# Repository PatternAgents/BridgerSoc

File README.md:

BridgerSoc
==========
PatternAgents BridgerSoc Control Shield for Arduino

[  
*PatternAgents BridgerSoc*](http://www.patternagents.com/projects/BridgerSoc.html)

PatternAgents The BridgerSoc uses a Programmable System-on-Chip that can read read inputs from sensors, 
switches, potentiometers, or other analog inputs and use those inputs to control the outputs of your choice.

Features:

  System-on-Chip Standalone Mode (Switches/Analog Inputs Control the Outputs)

  Arduino Uno/Leonardo/Mega/Due Compatible Shield

  Selectable 3.3Volt-5.0Volt Operation

  Sixteen (16) high power darlington control outputs

  Seven (7) analog inputs (sensors, potentiometers)

  Five (5) digital inputs (switches, sensors)

  UART, I2C, SPI, RS-485/DMX Interfaces

  Selectable mode of operation  (Manual or Interface/Shield controlled)

You can read more about the PSoC1 Integrated Circuit used here : http://www.cypress.com/?mpn=CY8C29566-24AXI

[  
*Licensing CC BY-NC-SA 4.0*](http://creativecommons.org/licenses/by-nc-sa/4.0/)

PatternAgents uses the increasingly popular business model called "Dual Licensing" 
in which both the open source software distribution mechanism and traditional commercial software distribution models are combined.

Open Source Projects:        

If you are developing and distributing open source applications under the Creative Commons CC BY-NC-SA 4.0, 
as published by the Creative Commons Foundation, then you are free to use the PatternAgents hardware/software under the CC BY-NC-SA 4.0 license. 
Please note that CC BY-NC-SA 4.0 requires that all modifications to the original code as well as all Derivative Works 
must also be released under the terms of the CC BY-NC-SA 4.0 license.

Closed Source Projects:

If you are developing and distributing traditional closed source or commercial applications, 
you must purchase a PatternAgents commercial use license, 
which is specifically designed for users interested in retaining the proprietary status of their designs and code. 
All PatternAgents commercial licenses expressly supersede the CC BY-NC-SA 4.0 license. 
This means that when you license the PatternAgents software under a commercial license, 
you specifically do not use the software under the CC BY-NC-SA 4.0 license and therefore you are not subject to any of its terms.
        
If you would like to use our designs for your own personal or educational use, have at it! 

Our public design repository is available at <a href="https://github.com/patternagents">Github</a>.

If you would like to produce our designs for commercial use, or as products for sale, 
please contact us to arrange for a Commercial Use license. We have many other designs, 
as well as options and extras that are not released publicly. 
We will also customize designs, firmware, and software for a reasonable fee, just contact us to discuss your requirements.

THIS SOFTWARE IS PROVIDED BY THE CONTRIBUTORS "AS IS" AND WITHOUT ANY EXPRESS OR IMPLIED WARRANTIES, 
INCLUDING, BUT NOT LIMITED TO, THE IMPLIED WARRANTIES OF MERCHANTABILITY AND FITNESS FOR A PARTICULAR PURPOSE ARE DISCLAIMED. 
IN NO EVENT SHALL THE COPYRIGHT OWNER OR CONTRIBUTORS BE LIABLE FOR ANY DIRECT, INDIRECT, INCIDENTAL, SPECIAL, EXEMPLARY, 
OR CONSEQUENTIAL DAMAGES (INCLUDING, BUT NOT LIMITED TO, PROCUREMENT OF SUBSTITUTE GOODS OR SERVICES; LOSS OF USE, DATA, 
OR PROFITS; OR BUSINESS INTERRUPTION) HOWEVER CAUSED AND ON ANY THEORY OF LIABILITY, WHETHER IN CONTRACT, 
STRICT LIABILITY, OR TORT (INCLUDING NEGLIGENCE OR OTHERWISE) ARISING IN ANY WAY OUT OF THE USE OF THIS SOFTWARE, 
EVEN IF ADVISED OF THE POSSIBILITY OF SUCH DAMAGE. 

-------------------------------------------------------------------------------------------

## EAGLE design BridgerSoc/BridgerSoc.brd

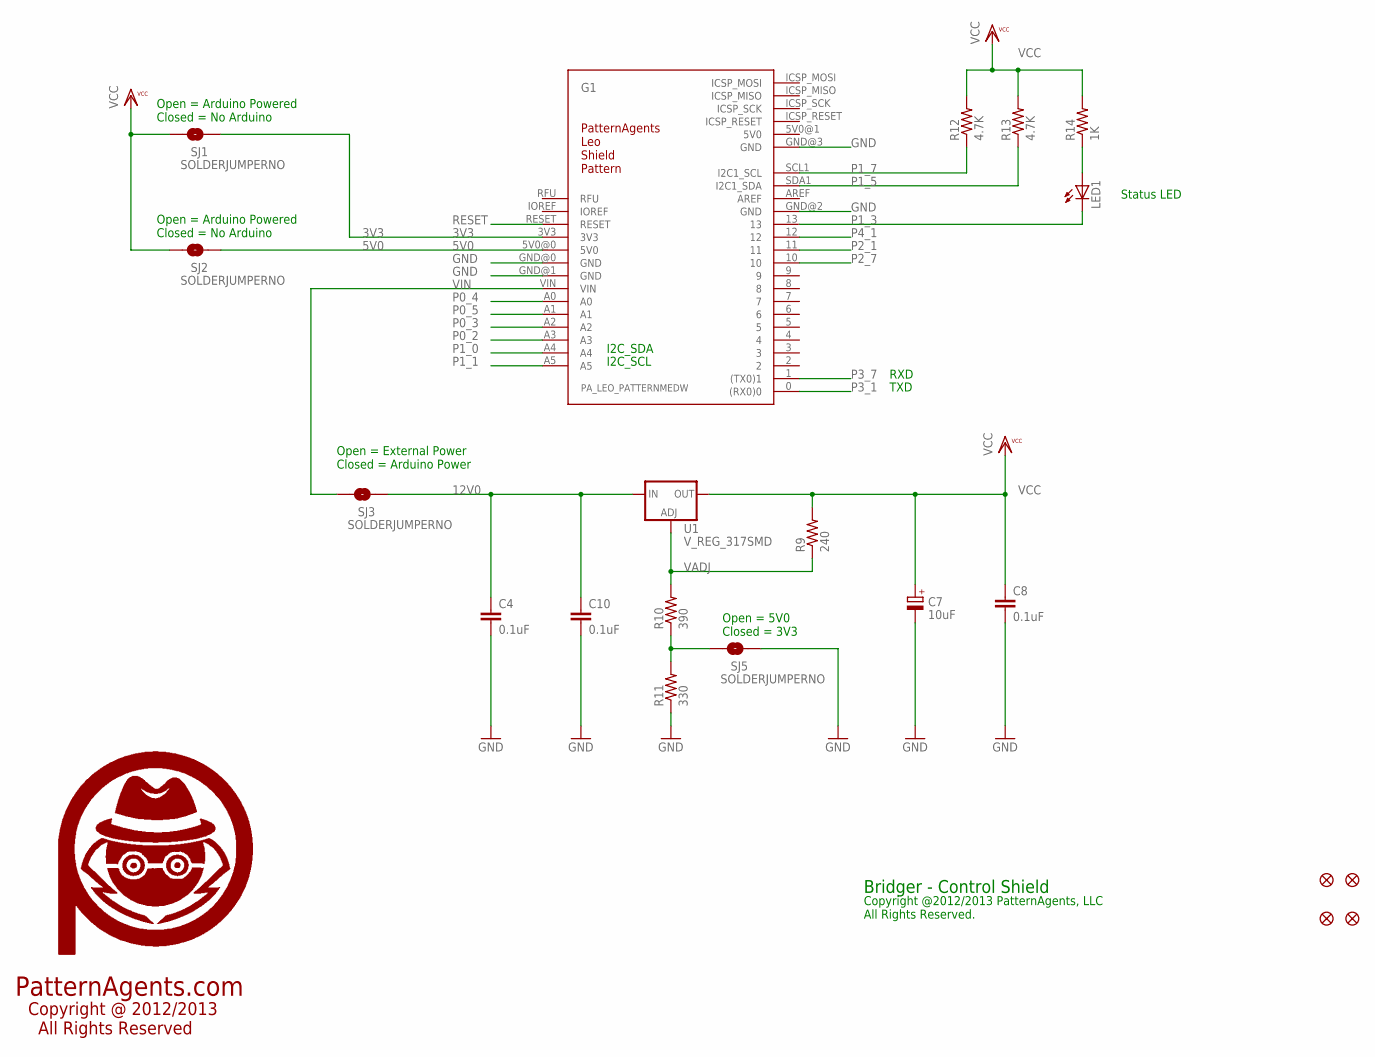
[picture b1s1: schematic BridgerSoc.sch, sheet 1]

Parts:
C4, C8, C10: 0.1uF; 0603-CAP
C7: 10uF; SMC_B
FID1, FID2, FID3, FID4: FIDUCIAL1.5X3; FIDUCIAL-1.5X3
G1: PA_LEO_PATTERNMEDW; PA_LEO_MEDW_PATTERN
LED1: LED0603; LED-0603
R9: 240; R0603
R10: 390; R0603
R11: 330; R0603
R12, R13: 4.7K; R0603
R14: 1K; R0603
SJ1, SJ2, SJ3, SJ5: SOLDERJUMPERNO; SJ_2S-NO
U1: V_REG_317SMD; SOT223
U$1: PA_LOGO_SYMLARGE; PA_LOGO_AGENT_LRG_SYM

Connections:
3V3: G1.3V3, SJ1.1
5V0: G1.5V0@0 (5V0), G1.5V0@1 (5V0), SJ2.1
12V0: C4.1, C10.1, SJ3.1, U1.3 (IN); also elsewhere on the board
GND: C4.2, C7.-, C8.2, C10.2, G1.GND@0 (GND), G1.GND@1 (GND), G1.GND@2 (GND), G1.GND@3 (GND), R11.1, SJ5.1; also elsewhere on the board
LED_D13: LED1.A, R14.1
P0_2: G1.A3; also elsewhere on the board
P0_3: G1.A2; also elsewhere on the board
P0_4: G1.A0; also elsewhere on the board
P0_5: G1.A1; also elsewhere on the board
P1_0: G1.A4; also elsewhere on the board
P1_1: G1.A5; also elsewhere on the board
P1_3: G1.13, LED1.C; also elsewhere on the board
P1_5: G1.SDA1 (I2C1_SDA), R13.1; also elsewhere on the board
P1_7: G1.SCL1 (I2C1_SCL), R12.1; also elsewhere on the board
P2_1: G1.11; also elsewhere on the board
P2_7: G1.10; also elsewhere on the board
P3_1: G1.0 ((RX0)0); also elsewhere on the board
P3_7: G1.1 ((TX0)1); also elsewhere on the board
P4_1: G1.12; also elsewhere on the board
RESET: G1.RESET
RFU: G1.RFU
V3_5: R10.1, R11.2, SJ5.2
VADJ: R9.1, R10.2, U1.1 (ADJ)
VCC: C7.+, C8.1, R9.2, R12.2, R13.2, R14.2, SJ1.2, SJ2.2, U1.2 (OUT); also elsewhere on the board
VIN: G1.VIN, SJ3.2

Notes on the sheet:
PatternAgents.com
Copyright @ 2012/2013 All Rights Reserved
Bridger - Control Shield
Copyright @2012/2013 PatternAgents, LLC All Rights Reserved.
I2C_SDA
I2C_SCL
Open = 5V0 Closed = 3V3
Open = External Power Closed = Arduino Power
Open = Arduino Powered Closed = No Arduino
TXD
RXD
Status LED

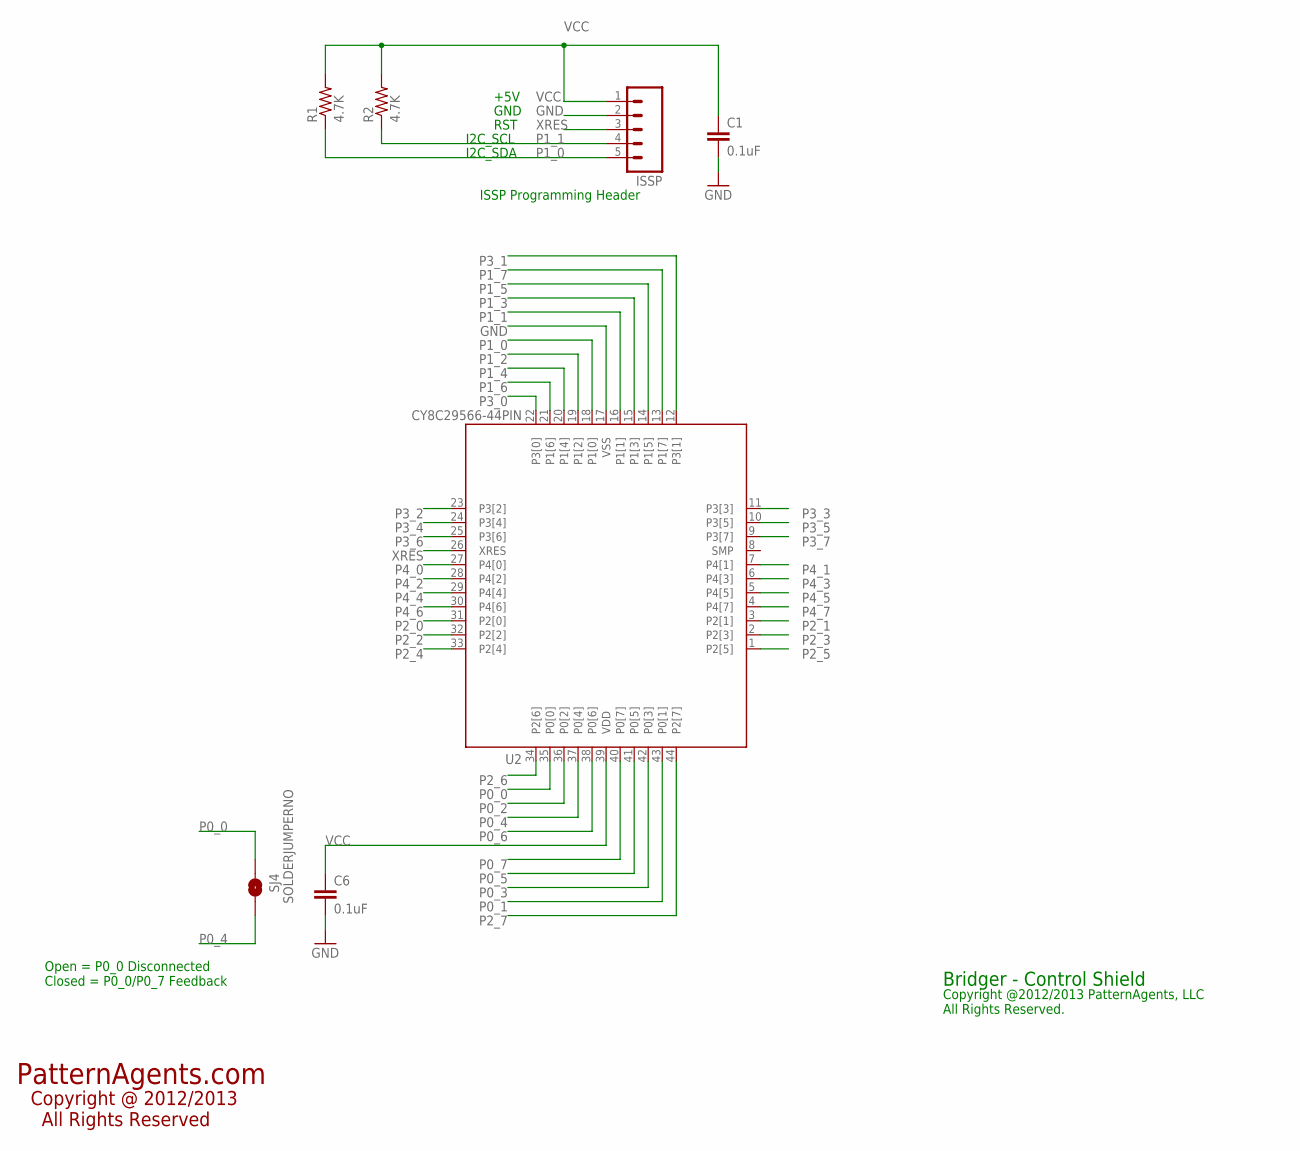
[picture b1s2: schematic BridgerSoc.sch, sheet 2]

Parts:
C1, C6: 0.1uF; 0603-CAP
ISSP: M05PTH; 1X05
R1, R2: 4.7K; R0603
SJ4: SOLDERJUMPERNO; SJ_2S-NO
U2: CY8C29566-44PIN; TQFP-10X10-44

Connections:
GND: C1.2, C6.2, ISSP.2, U2.17 (VSS); also elsewhere on the board
P0_0: SJ4.1, U2.35 (P0[0])
P0_1: U2.43 (P0[1]); also elsewhere on the board
P0_2: U2.36 (P0[2]); also elsewhere on the board
P0_3: U2.42 (P0[3]); also elsewhere on the board
P0_4: SJ4.2, U2.37 (P0[4]); also elsewhere on the board
P0_5: U2.41 (P0[5]); also elsewhere on the board
P0_6: U2.38 (P0[6]); also elsewhere on the board
P0_7: U2.40 (P0[7]); also elsewhere on the board
P1_0: ISSP.5, R1.1, U2.18 (P1[0]); also elsewhere on the board
P1_1: ISSP.4, R2.1, U2.16 (P1[1]); also elsewhere on the board
P1_2: U2.19 (P1[2]); also elsewhere on the board
P1_3: U2.15 (P1[3]); also elsewhere on the board
P1_4: U2.20 (P1[4]); also elsewhere on the board
P1_5: U2.14 (P1[5]); also elsewhere on the board
P1_6: U2.21 (P1[6]); also elsewhere on the board
P1_7: U2.13 (P1[7]); also elsewhere on the board
P2_0: U2.31 (P2[0]); also elsewhere on the board
P2_1: U2.3 (P2[1]); also elsewhere on the board
P2_2: U2.32 (P2[2]); also elsewhere on the board
P2_3: U2.2 (P2[3]); also elsewhere on the board
P2_4: U2.33 (P2[4]); also elsewhere on the board
P2_5: U2.1 (P2[5]); also elsewhere on the board
P2_6: U2.34 (P2[6]); also elsewhere on the board
P2_7: U2.44 (P2[7]); also elsewhere on the board
P3_0: U2.22 (P3[0]); also elsewhere on the board
P3_1: U2.12 (P3[1]); also elsewhere on the board
P3_2: U2.23 (P3[2]); also elsewhere on the board
P3_3: U2.11 (P3[3]); also elsewhere on the board
P3_4: U2.24 (P3[4]); also elsewhere on the board
P3_5: U2.10 (P3[5]); also elsewhere on the board
P3_6: U2.25 (P3[6]); also elsewhere on the board
P3_7: U2.9 (P3[7]); also elsewhere on the board
P4_0: U2.27 (P4[0]); also elsewhere on the board
P4_1: U2.7 (P4[1]); also elsewhere on the board
P4_2: U2.28 (P4[2]); also elsewhere on the board
P4_3: U2.6 (P4[3]); also elsewhere on the board
P4_4: U2.29 (P4[4]); also elsewhere on the board
P4_5: U2.5 (P4[5]); also elsewhere on the board
P4_6: U2.30 (P4[6]); also elsewhere on the board
P4_7: U2.4 (P4[7]); also elsewhere on the board
SMP: U2.8 (SMP)
VCC: C1.1, C6.1, ISSP.1, R1.2, R2.2, U2.39 (VDD); also elsewhere on the board
XRES: ISSP.3, U2.26 (XRES)

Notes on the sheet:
PatternAgents.com
Copyright @ 2012/2013 All Rights Reserved
Bridger - Control Shield
Copyright @2012/2013 PatternAgents, LLC All Rights Reserved.
ISSP Programming Header
I2C_SDA
I2C_SCL
RST
GND
+5V
Open = P0_0 Disconnected Closed = P0_0/P0_7 Feedback

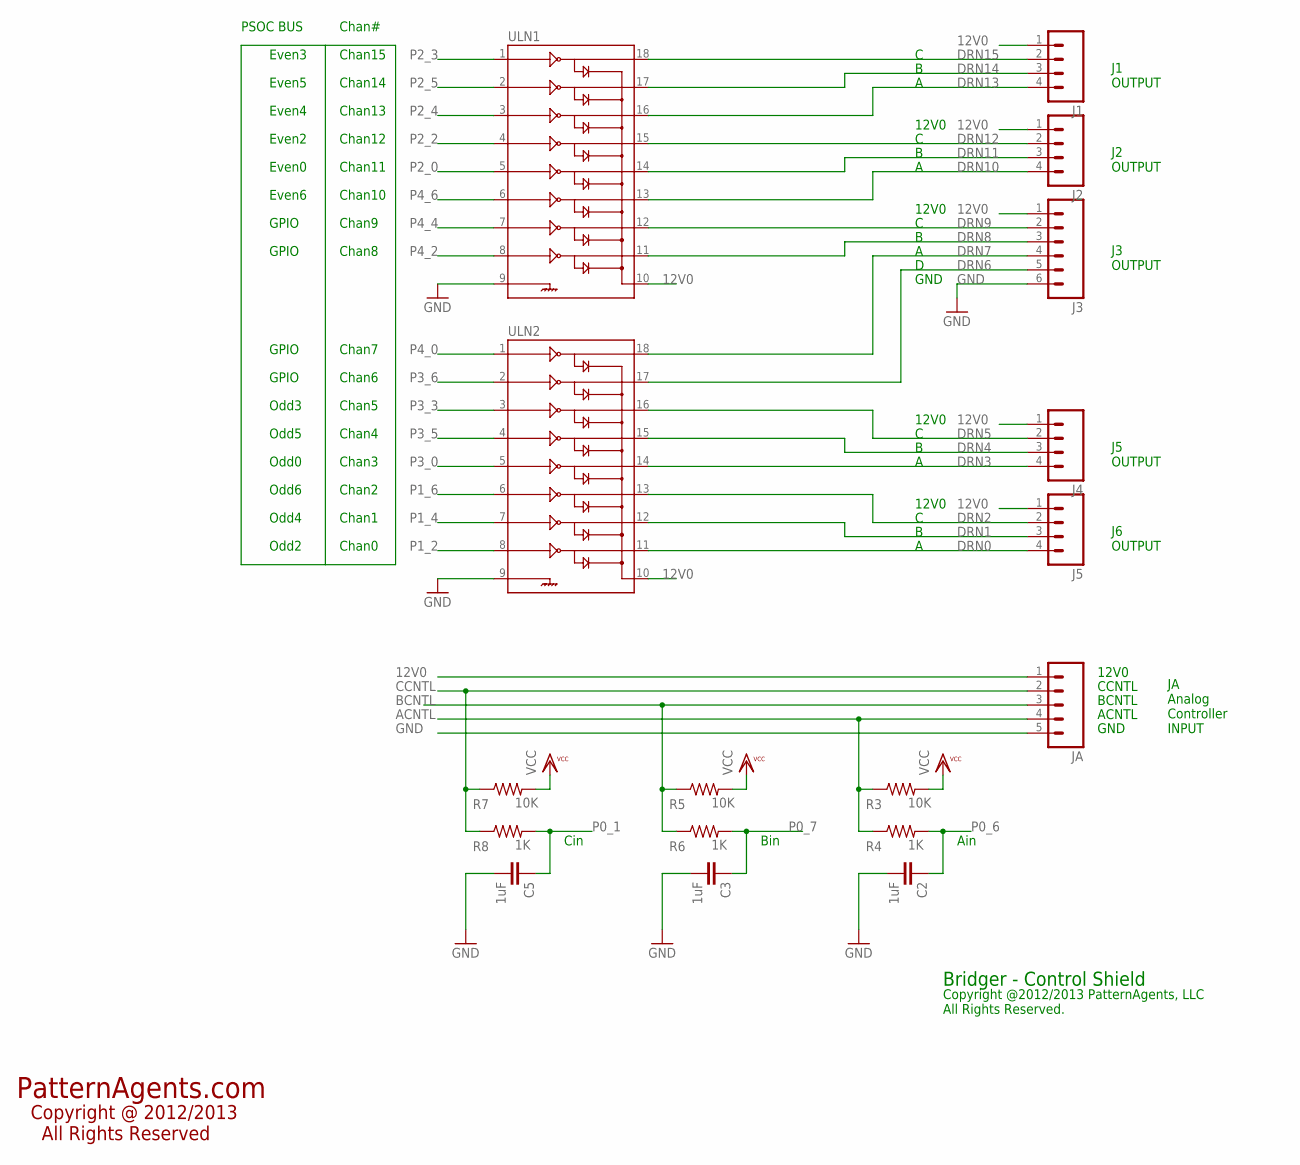
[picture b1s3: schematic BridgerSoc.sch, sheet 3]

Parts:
C2, C3, C5: 1uF; 0603-CAP
J1, J2, J4, J5: M04PTH; 1X04
J3: M06SIP; 1X06
JA: M05PTH; 1X05
R3, R5, R7: 10K; R0603
R4, R6, R8: 1K; R0603
ULN1, ULN2: ULN2803SOICW; SO18L

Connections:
12V0: J1.1, J2.1, J3.1, J4.1, J5.1, JA.1, ULN1.10, ULN2.10; also elsewhere on the board
ACNTL: JA.4, R3.1, R4.1
BCNTL: JA.3, R5.1, R6.1
CCNTL: JA.2, R7.1, R8.1
DRN0: J5.4, ULN2.11
DRN1: J5.3, ULN2.12
DRN2: J5.2, ULN2.13
DRN3: J4.4, ULN2.14
DRN4: J4.3, ULN2.15
DRN5: J4.2, ULN2.16
DRN6: J3.5, ULN2.17
DRN7: J3.4, ULN2.18
DRN8: J3.3, ULN1.11
DRN9: J3.2, ULN1.12
DRN10: J2.4, ULN1.13
DRN11: J2.3, ULN1.14
DRN12: J2.2, ULN1.15
DRN13: J1.4, ULN1.16
DRN14: J1.3, ULN1.17
DRN15: J1.2, ULN1.18
GND: C2.2, C3.2, C5.2, J3.6, JA.5, ULN1.9, ULN2.9; also elsewhere on the board
P0_1: C5.1, R8.2; also elsewhere on the board
P0_6: C2.1, R4.2; also elsewhere on the board
P0_7: C3.1, R6.2; also elsewhere on the board
P1_2: ULN2.8; also elsewhere on the board
P1_4: ULN2.7; also elsewhere on the board
P1_6: ULN2.6; also elsewhere on the board
P2_0: ULN1.5; also elsewhere on the board
P2_2: ULN1.4; also elsewhere on the board
P2_3: ULN1.1; also elsewhere on the board
P2_4: ULN1.3; also elsewhere on the board
P2_5: ULN1.2; also elsewhere on the board
P3_0: ULN2.5; also elsewhere on the board
P3_3: ULN2.3; also elsewhere on the board
P3_5: ULN2.4; also elsewhere on the board
P3_6: ULN2.2; also elsewhere on the board
P4_0: ULN2.1; also elsewhere on the board
P4_2: ULN1.8; also elsewhere on the board
P4_4: ULN1.7; also elsewhere on the board
P4_6: ULN1.6; also elsewhere on the board
VCC: R3.2, R5.2, R7.2; also elsewhere on the board

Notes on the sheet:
Bridger - Control Shield
Copyright @2012/2013 PatternAgents, LLC All Rights Reserved.
PatternAgents.com
Copyright @ 2012/2013 All Rights Reserved
12V0
GND
ACNTL
BCNTL
CCNTL
JA Analog Controller INPUT
J6 OUTPUT
J5 OUTPUT
J3 OUTPUT
J2 OUTPUT
J1 OUTPUT
Cin
Bin
Ain
Chan0
Chan1
Chan2
Chan3
Chan4
Chan5
Chan6
Chan7
Chan8
Chan9
Chan10
Chan11
Chan12
Chan13
Chan14
Chan15
Odd2
Odd4
Odd6
Odd0
Odd3
Odd5

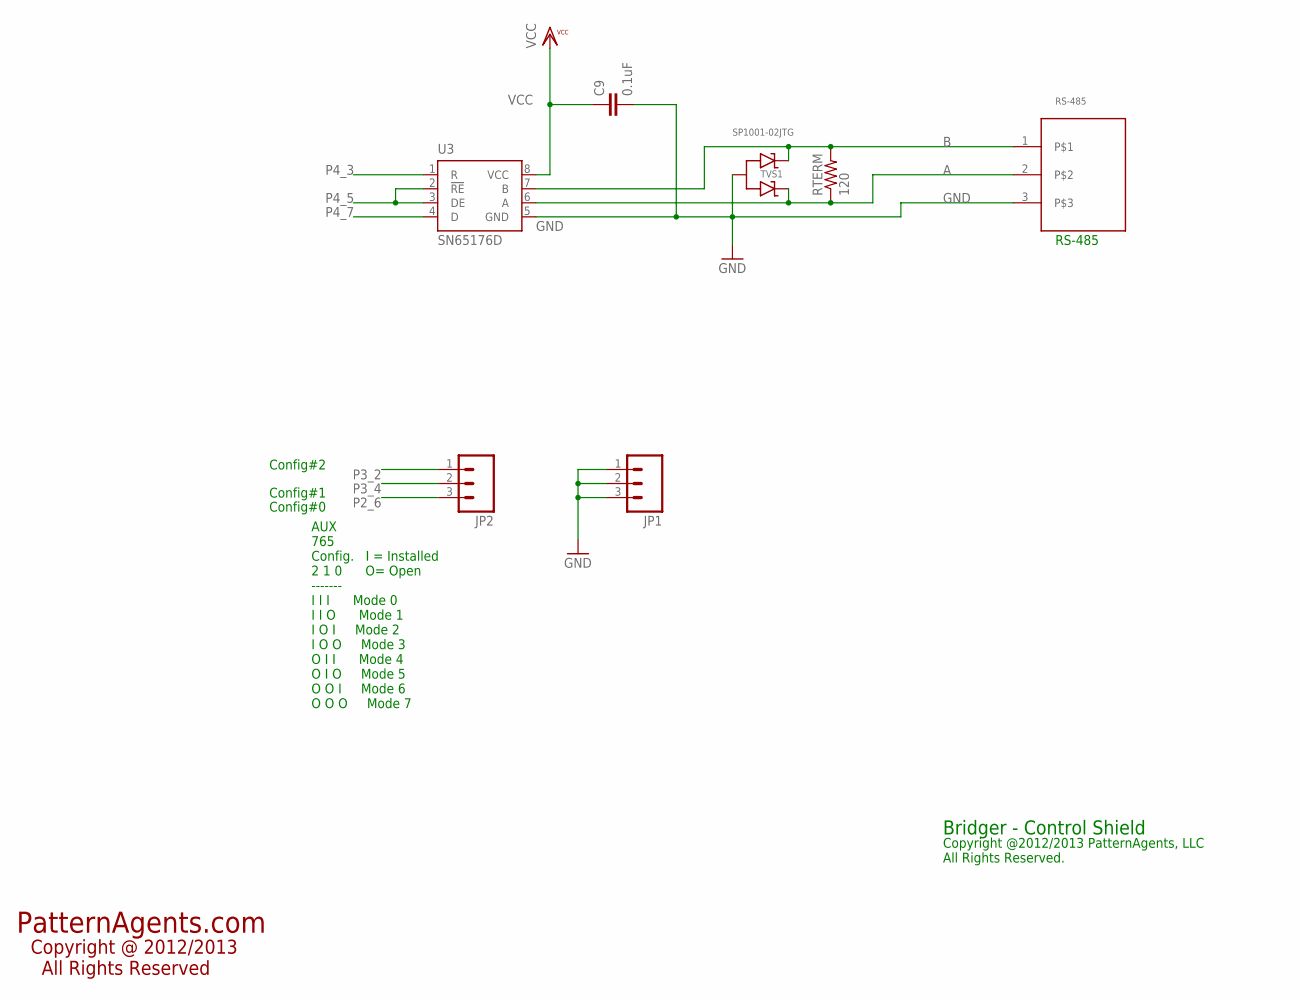
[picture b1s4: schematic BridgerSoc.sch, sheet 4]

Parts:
C9: 0.1uF; 0603-CAP
JP1, JP2: M03PTH; 1X03
RS-485: 70553-02
RTERM: 120; 0603-RES
TVS1: SP1001-02JTG; SC70-3
U3: SN65176D; SO-08

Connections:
A: RS-485.2, RTERM.1, TVS1.2 (C2), U3.6 (A)
B: RS-485.1, RTERM.2, TVS1.1 (C1), U3.7 (B)
GND: C9.2, JP1.1, JP1.2, JP1.3, RS-485.3, TVS1.3 (A), U3.5 (GND); also elsewhere on the board
P2_6: JP2.3; also elsewhere on the board
P3_2: JP2.1; also elsewhere on the board
P3_4: JP2.2; also elsewhere on the board
P4_3: U3.1 (R); also elsewhere on the board
P4_5: U3.2 (!RE), U3.3 (DE); also elsewhere on the board
P4_7: U3.4 (D); also elsewhere on the board
VCC: C9.1, U3.8 (VCC); also elsewhere on the board

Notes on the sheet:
RS-485
PatternAgents.com
Copyright @ 2012/2013 All Rights Reserved
Bridger - Control Shield
Copyright @2012/2013 PatternAgents, LLC All Rights Reserved.
Config#2
Config#1
Config#0
AUX 765 Config. I = Installed 2 1 0 O= Open ------- I I I Mode 0 I I O Mode 1 I O I Mode 2 I O O Mode 3 O I I Mode 4 O I O Mode 5 O O I Mode 6 O O O Mode 7

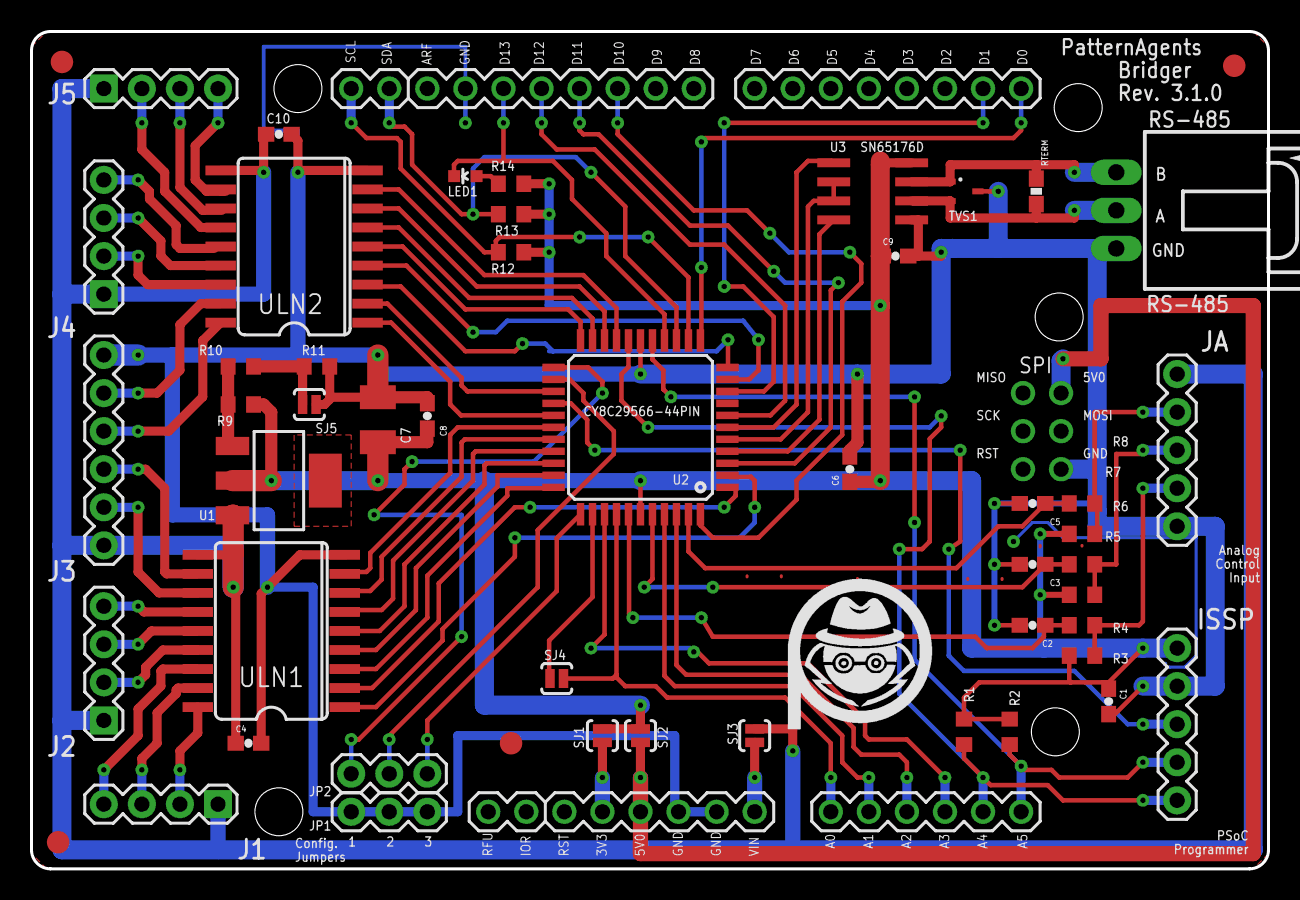
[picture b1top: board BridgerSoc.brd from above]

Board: 2 copper layers, 82.6 x 55.9 mm, 54 parts (1 on the bottom side), 71 nets.

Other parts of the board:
U$9: PA_LOGO_AGENT_LRG_SYM

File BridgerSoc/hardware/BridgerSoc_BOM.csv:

"Part";"Value";"Device";"Package";"Description";"MF";"MPN";"OC_FARNELL";"OC_NEWARK";
"C1";"0.1uF";"CAP0603-CAP";"0603-CAP";"Capacitor";"";"";"";"";
"C2";"1uF";"CAP0603-CAP";"0603-CAP";"Capacitor";"";"";"";"";
"C3";"1uF";"CAP0603-CAP";"0603-CAP";"Capacitor";"";"";"";"";
"C4";"0.1uF";"CAP0603-CAP";"0603-CAP";"Capacitor";"";"";"";"";
"C5";"1uF";"CAP0603-CAP";"0603-CAP";"Capacitor";"";"";"";"";
"C6";"0.1uF";"CAP0603-CAP";"0603-CAP";"Capacitor";"";"";"";"";
"C7";"10uF";"CPOL-EUSMCB";"SMC_B";"POLARIZED CAPACITOR, European symbol";"";"";"";"";
"C8";"0.1uF";"CAP0603-CAP";"0603-CAP";"Capacitor";"";"";"";"";
"C9";"0.1uF";"CAP0603-CAP";"0603-CAP";"Capacitor";"";"";"";"";
"C10";"0.1uF";"CAP0603-CAP";"0603-CAP";"Capacitor";"";"";"";"";
"FID1";"FIDUCIAL1.5X3";"FIDUCIAL1.5X3";"FIDUCIAL-1.5X3";"Fiducial Alignment Points";"";"";"";"";
"FID2";"FIDUCIAL1.5X3";"FIDUCIAL1.5X3";"FIDUCIAL-1.5X3";"Fiducial Alignment Points";"";"";"";"";
"FID3";"FIDUCIAL1.5X3";"FIDUCIAL1.5X3";"FIDUCIAL-1.5X3";"Fiducial Alignment Points";"";"";"";"";
"FID4";"FIDUCIAL1.5X3";"FIDUCIAL1.5X3";"FIDUCIAL-1.5X3";"Fiducial Alignment Points";"";"";"";"";
"G1";"PA_LEO_PATTERNMEDW";"PA_LEO_PATTERNMEDW";"PA_LEO_MEDW_PATTERN";"PatternAgents Leo Shield Pattern";"";"";"";"";
"ISSP";"";"M05PTH";"1X05";"Header 5";"";"";"";"";
"J1";"";"M04PTH";"1X04";"Header 4";"";"";"";"";
"J2";"";"M04PTH";"1X04";"Header 4";"";"";"";"";
"J3";"";"M06SIP";"1X06";"Header 6";"";"";"";"";
"J4";"";"M04PTH";"1X04";"Header 4";"";"";"";"";
"J5";"";"M04PTH";"1X04";"Header 4";"";"";"";"";
"JA";"";"M05PTH";"1X05";"Header 5";"";"";"";"";
"JP1";"";"M03PTH";"1X03";"Header 3";"";"";"";"";
"JP2";"";"M03PTH";"1X03";"Header 3";"";"";"";"";
"LED1";"";"LED0603";"LED-0603";"LEDs";"";"";"";"";
"R1";"4.7K";"RESISTORR0603";"R0603";"RESISTOR, American symbol";"";"";"";"";
"R2";"4.7K";"RESISTORR0603";"R0603";"RESISTOR, American symbol";"";"";"";"";
"R3";"10K";"RESISTORR0603";"R0603";"RESISTOR, American symbol";"";"";"";"";
"R4";"1K";"RESISTORR0603";"R0603";"RESISTOR, American symbol";"";"";"";"";
"R5";"10K";"RESISTORR0603";"R0603";"RESISTOR, American symbol";"";"";"";"";
"R6";"1K";"RESISTORR0603";"R0603";"RESISTOR, American symbol";"";"";"";"";
"R7";"10K";"RESISTORR0603";"R0603";"RESISTOR, American symbol";"";"";"";"";
"R8";"1K";"RESISTORR0603";"R0603";"RESISTOR, American symbol";"";"";"";"";
"R9";"240";"RESISTORR0603";"R0603";"RESISTOR, American symbol";"";"";"";"";
"R10";"390";"RESISTORR0603";"R0603";"RESISTOR, American symbol";"";"";"";"";
"R11";"330";"RESISTORR0603";"R0603";"RESISTOR, American symbol";"";"";"";"";
"R12";"4.7K";"RESISTORR0603";"R0603";"RESISTOR, American symbol";"";"";"";"";
"R13";"4.7K";"RESISTORR0603";"R0603";"RESISTOR, American symbol";"";"";"";"";
"R14";"1K";"RESISTORR0603";"R0603";"RESISTOR, American symbol";"";"";"";"";
"RS-485";"70553-02";"70553-02";"70553-02";"Molex SL Modular Connectors - 3 PIN";"";"";"";"";
"RTERM";"120";"RESISTOR_SFE0603-RES";"0603-RES";"Resistor";"";"";"";"";
"SJ1";"SOLDERJUMPERNO";"SOLDERJUMPERNO";"SJ_2S-NO";"Solder Jumper";"";"";"";"";
"SJ2";"SOLDERJUMPERNO";"SOLDERJUMPERNO";"SJ_2S-NO";"Solder Jumper";"";"";"";"";
"SJ3";"SOLDERJUMPERNO";"SOLDERJUMPERNO";"SJ_2S-NO";"Solder Jumper";"";"";"";"";
"SJ4";"SOLDERJUMPERNO";"SOLDERJUMPERNO";"SJ_2S-NO";"Solder Jumper";"";"";"";"";
"SJ5";"SOLDERJUMPERNO";"SOLDERJUMPERNO";"SJ_2S-NO";"Solder Jumper";"";"";"";"";
"TVS1";"SP1001-02JTG";"SP1001-02JTG";"SC70-3";"Littelfuse SP1001-02JTG TVS Diode Array 8pf 15kV Source: http://www.littelfuse.com/data/en/Product_Catalogs/Littelfus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 patternshed.com: created 3/25/2012";"";"";"";"";
"U$1";"PA_LOGO_SYMLARGE";"PA_LOGO_SYMLARGE";"PA_LOGO_AGENT_LRG_SYM";"PatternAgents Logo Symbol";"";"";"";"";
"U1";"V_REG_317SMD";"V_REG_317SMD";"SOT223";"Voltage Regulator";"";"";"";"";
"U2";"CY8C29566-44PIN";"CY8C29566-44PIN";"TQFP-10X10-44";"Cypress PSoC® 1 - Programmable System on Chip, M8C Based";"";"";"";"";
"U3";"SN65176D";"SN65176D";"SO-08";"DIFFERENTIAL BUS TRANSCEIVER";"TEXAS INSTRUMENTS";"SN65176BD";"9589970";"08F5891";
"ULN1";"";"ULN2803SOICW";"SO18L";"Darlington Driver";"";"";"";"";
"ULN2";"";"ULN2803SOICW";"SO18L";"Darlington Driver";"";"";"";"";

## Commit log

2013-07-17 initial project creation
2013-07-17 Fix Title
2013-07-18 Fix Typos
2013-07-18 fix links
2013-07-19 link fixes
2013-07-22 reduce png file sizes
2013-07-29 Create gh-pages branch via GitHub
2013-11-17 Initial Production Release
    EagleCAD & EagleUp source files
    Datasheets for Components
    BOM and Gerbers
2013-12-23 Move Licensing to CC 4.0
    Resolve licensing discrepancies, move to CC 4.0 everywhere.
2013-12-28 Update gh-pages
2013-12-28 Update README to match Master Branch
2013-12-28 Update README, remove duplicate tagline
2013-12-28 Update README - remove duplicate tagline
2013-12-30 Add Redirect
2013-12-30 Try Again...
2013-12-30 remove dangling directory
2013-12-31 remove windows thumbnails...
2014-01-05 rename legalcode.txt to LICENSE for consistancy

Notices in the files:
parts and their libraries:
SparkFun-PowerIC: Licensing: CC v3.0 Share-Alike You are welcome to use this library for commercial purposes.
PatternAgents-Boards: License : http://creativecommons.org/licenses/by-sa/2.5
(Creative Commons 2.5)
PatternAgents-Logos: License : http://creativecommons.org/licenses/by-sa/3.0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
